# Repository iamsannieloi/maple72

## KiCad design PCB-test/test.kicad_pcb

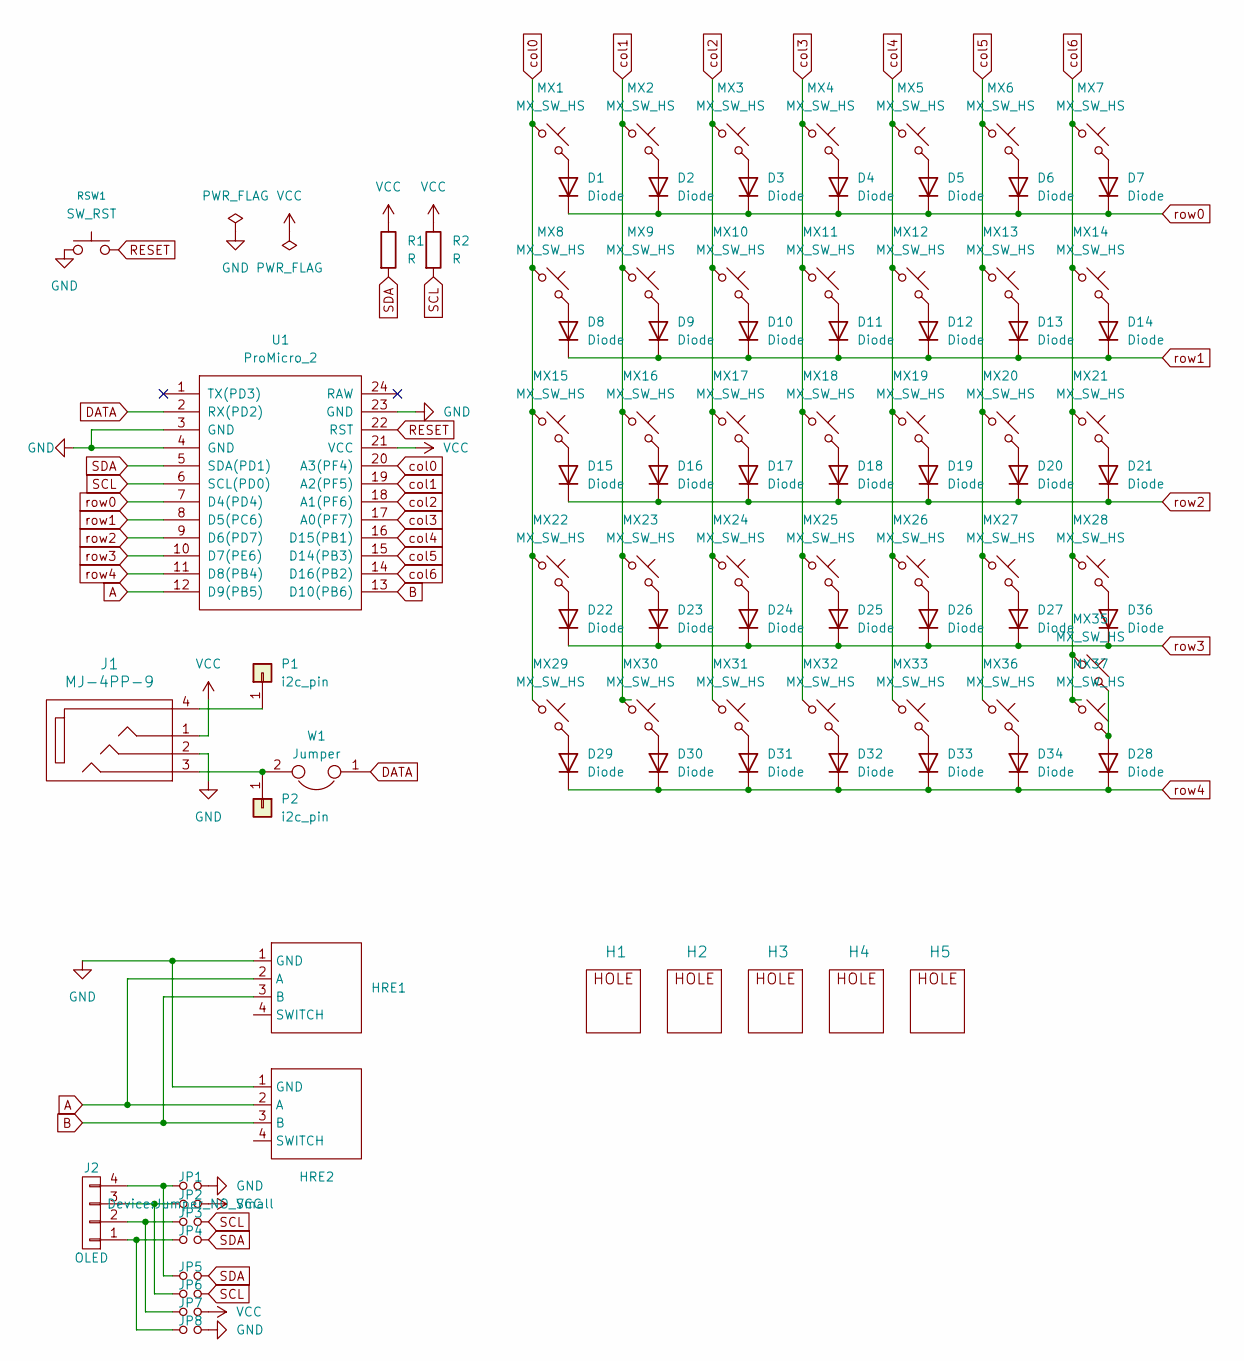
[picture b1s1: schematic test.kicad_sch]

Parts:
D1, D2, D3, D4, D5, D6, D7, D8, D9, D10, D11, D12, D13, D14, D15, D16, D17, D18, D19, D20, D21, D22, D23, D24, D25, D26, D27, D28, D29, D30, D31, D32, D33, D34, D36: Diode; Diode_TH_SOD123
H1, H2, H3, H4, H5: HOLE; HOLE_M2_TH
HRE1, HRE2: RollerEncoder_Panasonic_EVQWGD001
J1: MJ-4PP-9
J2: OLED; OLED_4Pin
JP1, JP2, JP3, JP4, JP5, JP6, JP7, JP8: Device:Jumper_NO_Small; Jumper
MX1, MX2, MX3, MX4, MX5, MX6, MX7, MX8, MX9, MX10, MX11, MX12, MX13, MX14, MX15, MX16, MX17, MX18, MX19, MX20, MX21, MX22, MX23, MX24, MX25, MX26, MX27, MX28, MX29, MX30, MX31, MX32, MX33, MX35, MX36, MX37: MX_SW_HS; MX_Socket_18mm
P1, P2: i2c_pin; 1pin_conn
R1, R2: R; RESISTOR_mini
RSW1: SW_RST; TACT_SWITCH_TVBP06
U1: ProMicro_2; ProMicro_rev2
W1: Jumper; jumper_data

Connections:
A: HRE1.2 (A), HRE2.2 (A), U1.12 (D9(PB5))
B: HRE1.3 (B), HRE2.3 (B), U1.13 (D10(PB6))
DATA: U1.2 (RX(PD2)), W1.1
GND: HRE1.1 (GND), HRE2.1 (GND), J1.2, JP1.2, JP8.2, RSW1.1, U1.3 (GND), U1.4 (GND), U1.23 (GND)
unnamed: D1.2 (A), MX1.2
unnamed: D2.2 (A), MX2.2
unnamed: D3.2 (A), MX3.2
unnamed: D4.2 (A), MX4.2
unnamed: D5.2 (A), MX5.2
unnamed: D6.2 (A), MX6.2
unnamed: D7.2 (A), MX7.2
unnamed: D8.2 (A), MX8.2
unnamed: D9.2 (A), MX9.2
unnamed: D10.2 (A), MX10.2
unnamed: D11.2 (A), MX11.2
unnamed: D12.2 (A), MX12.2
unnamed: D13.2 (A), MX13.2
unnamed: D14.2 (A), MX14.2
unnamed: D15.2 (A), MX15.2
unnamed: D16.2 (A), MX16.2
unnamed: D17.2 (A), MX17.2
unnamed: D18.2 (A), MX18.2
unnamed: D19.2 (A), MX19.2
unnamed: D20.2 (A), MX20.2
unnamed: D21.2 (A), MX21.2
unnamed: D22.2 (A), MX22.2
unnamed: D23.2 (A), MX23.2
unnamed: D24.2 (A), MX24.2
unnamed: D25.2 (A), MX25.2
unnamed: D26.2 (A), MX26.2
unnamed: D27.2 (A), MX27.2
unnamed: D28.2 (A), MX35.2, MX37.2
unnamed: D29.2 (A), MX29.2
unnamed: D30.2 (A), MX30.2
unnamed: D31.2 (A), MX31.2
unnamed: D32.2 (A), MX32.2
unnamed: D33.2 (A), MX33.2
unnamed: D34.2 (A), MX36.2
unnamed: D36.2 (A), MX28.2
unnamed: J2.1, JP4.1, JP8.1
unnamed: J2.2, JP3.1, JP7.1
unnamed: J2.3, JP2.1, JP6.1
unnamed: J2.4, JP1.1, JP5.1
unnamed: J1.4, P1.1
unnamed: J1.3, P2.1, W1.2
RESET: RSW1.2, U1.22 (RST)
SCL: JP3.2, JP6.2, R2.2, U1.6 (SCL(PD0))
SDA: JP4.2, JP5.2, R1.2, U1.5 (SDA(PD1))
VCC: J1.1, JP2.2, JP7.2, R1.1, R2.1, U1.21 (VCC)
col0: MX1.1, MX8.1, MX15.1, MX22.1, MX29.1, U1.20 (A3(PF4))
col1: MX2.1, MX9.1, MX16.1, MX23.1, MX30.1, U1.19 (A2(PF5))
col2: MX3.1, MX10.1, MX17.1, MX24.1, MX31.1, U1.18 (A1(PF6))
col3: MX4.1, MX11.1, MX18.1, MX25.1, MX32.1, U1.17 (A0(PF7))
col4: MX5.1, MX12.1, MX19.1, MX26.1, MX33.1, U1.16 (D15(PB1))
col5: MX6.1, MX13.1, MX20.1, MX27.1, MX36.1, U1.15 (D14(PB3))
col6: MX7.1, MX14.1, MX21.1, MX28.1, MX35.1, MX37.1, U1.14 (D16(PB2))
row0: D1.1 (K), D2.1 (K), D3.1 (K), D4.1 (K), D5.1 (K), D6.1 (K), D7.1 (K), U1.7 (D4(PD4))
row1: D8.1 (K), D9.1 (K), D10.1 (K), D11.1 (K), D12.1 (K), D13.1 (K), D14.1 (K), U1.8 (D5(PC6))
row2: D15.1 (K), D16.1 (K), D17.1 (K), D18.1 (K), D19.1 (K), D20.1 (K), D21.1 (K), U1.9 (D6(PD7))
row3: D22.1 (K), D23.1 (K), D24.1 (K), D25.1 (K), D26.1 (K), D27.1 (K), D36.1 (K), U1.10 (D7(PE6))
row4: D28.1 (K), D29.1 (K), D30.1 (K), D31.1 (K), D32.1 (K), D33.1 (K), D34.1 (K), U1.11 (D8(PB4))

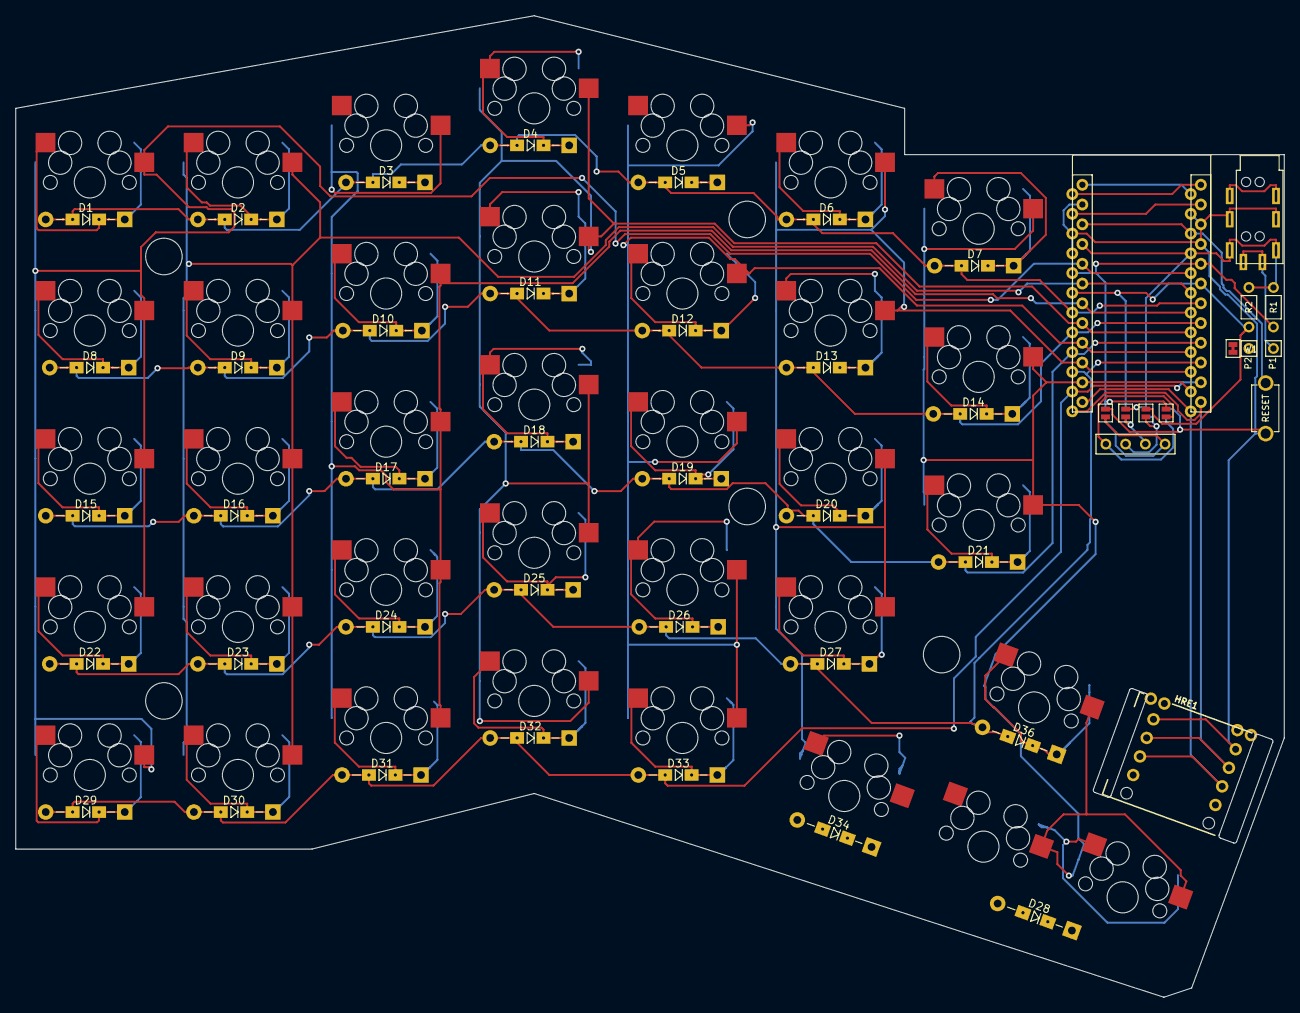
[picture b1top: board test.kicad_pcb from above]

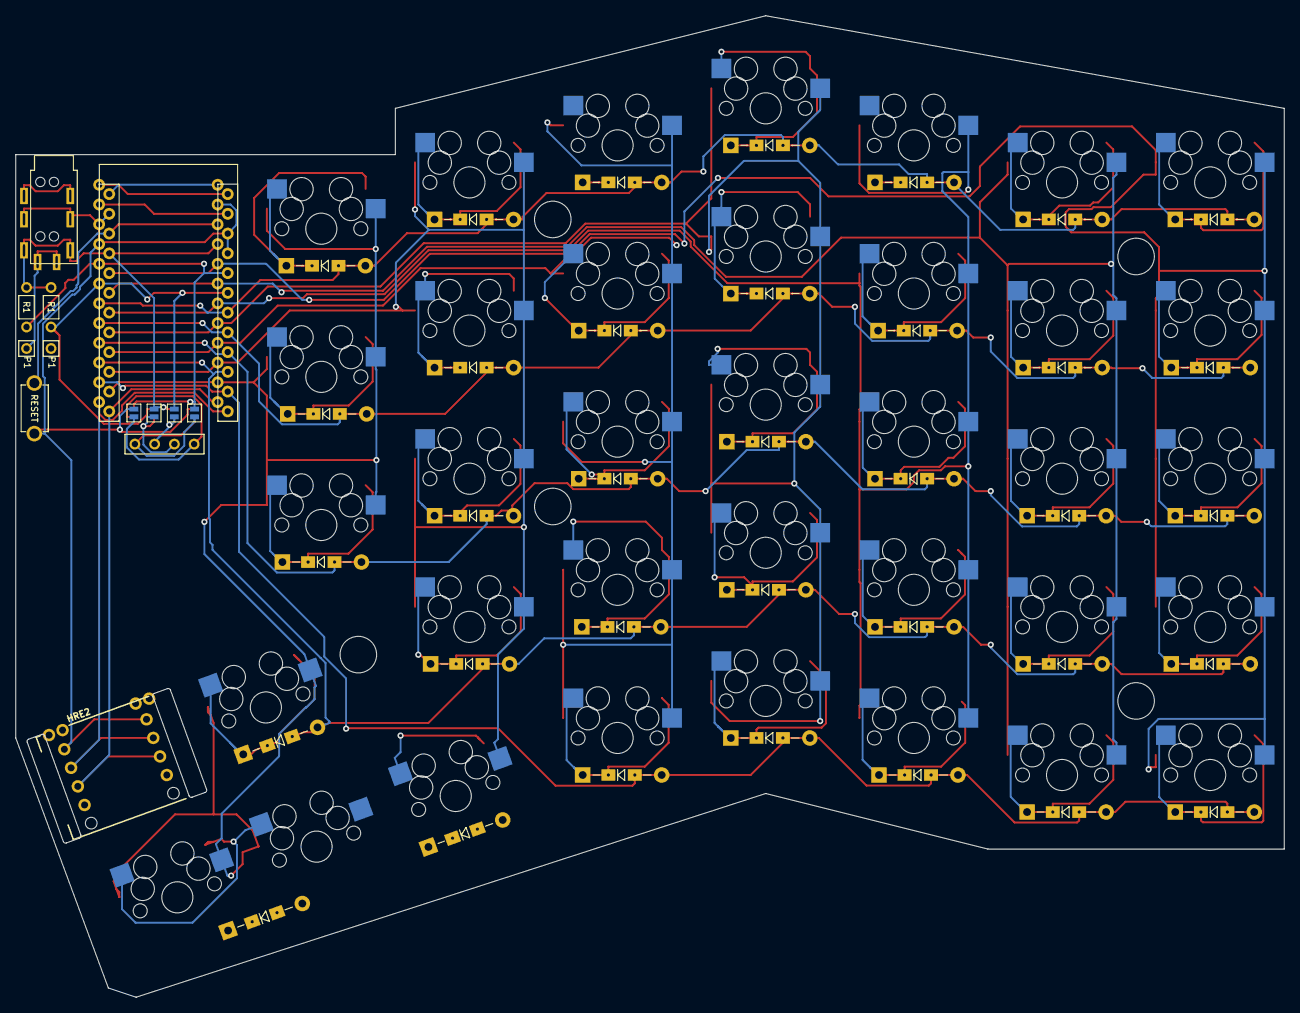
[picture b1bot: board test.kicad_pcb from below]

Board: 2 copper layers, 163.1 x 126.2 mm, 95 parts (6 on the bottom side), 61 nets.

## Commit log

2023-12-05 adding initial files for keyboard
2023-12-05 adding folder for playing around with pcb
